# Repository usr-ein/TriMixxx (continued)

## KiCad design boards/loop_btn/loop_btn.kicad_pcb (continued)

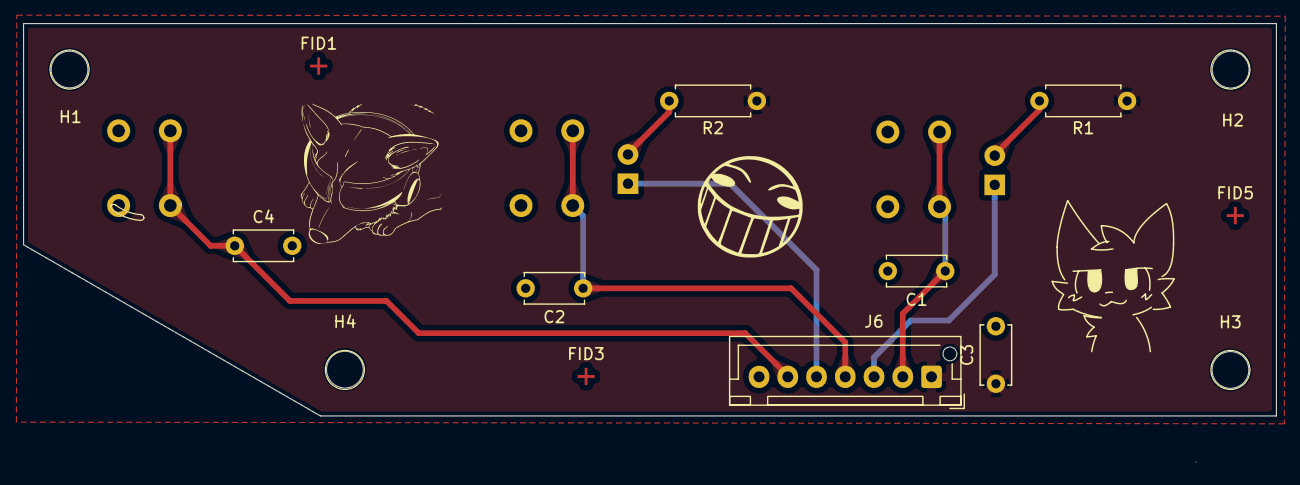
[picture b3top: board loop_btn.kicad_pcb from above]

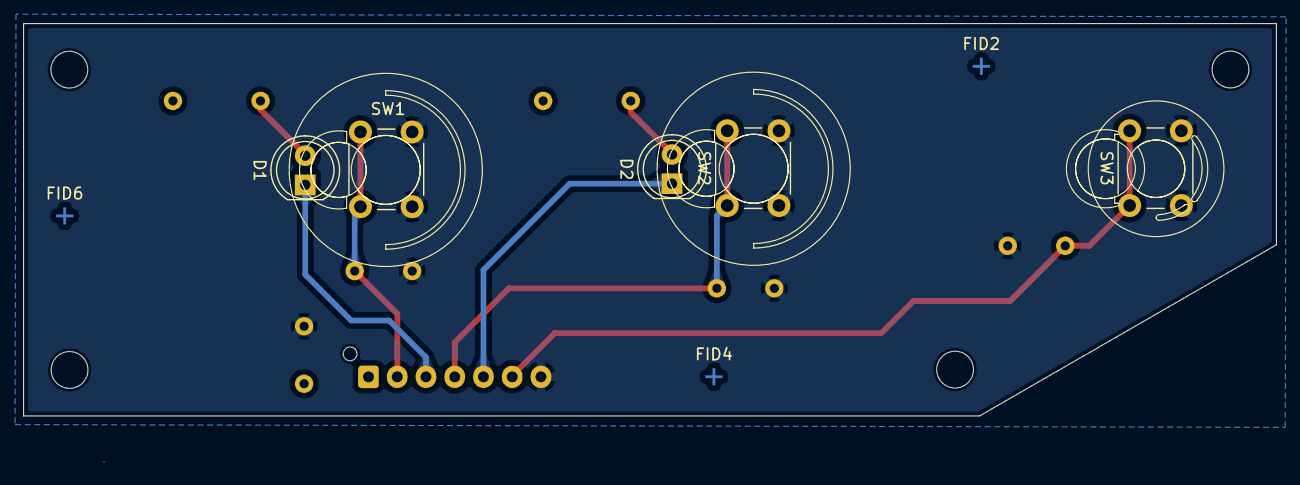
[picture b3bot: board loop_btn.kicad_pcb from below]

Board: 2 copper layers, 109.0 x 34.1 mm, 22 parts (8 on the bottom side), 9 nets.

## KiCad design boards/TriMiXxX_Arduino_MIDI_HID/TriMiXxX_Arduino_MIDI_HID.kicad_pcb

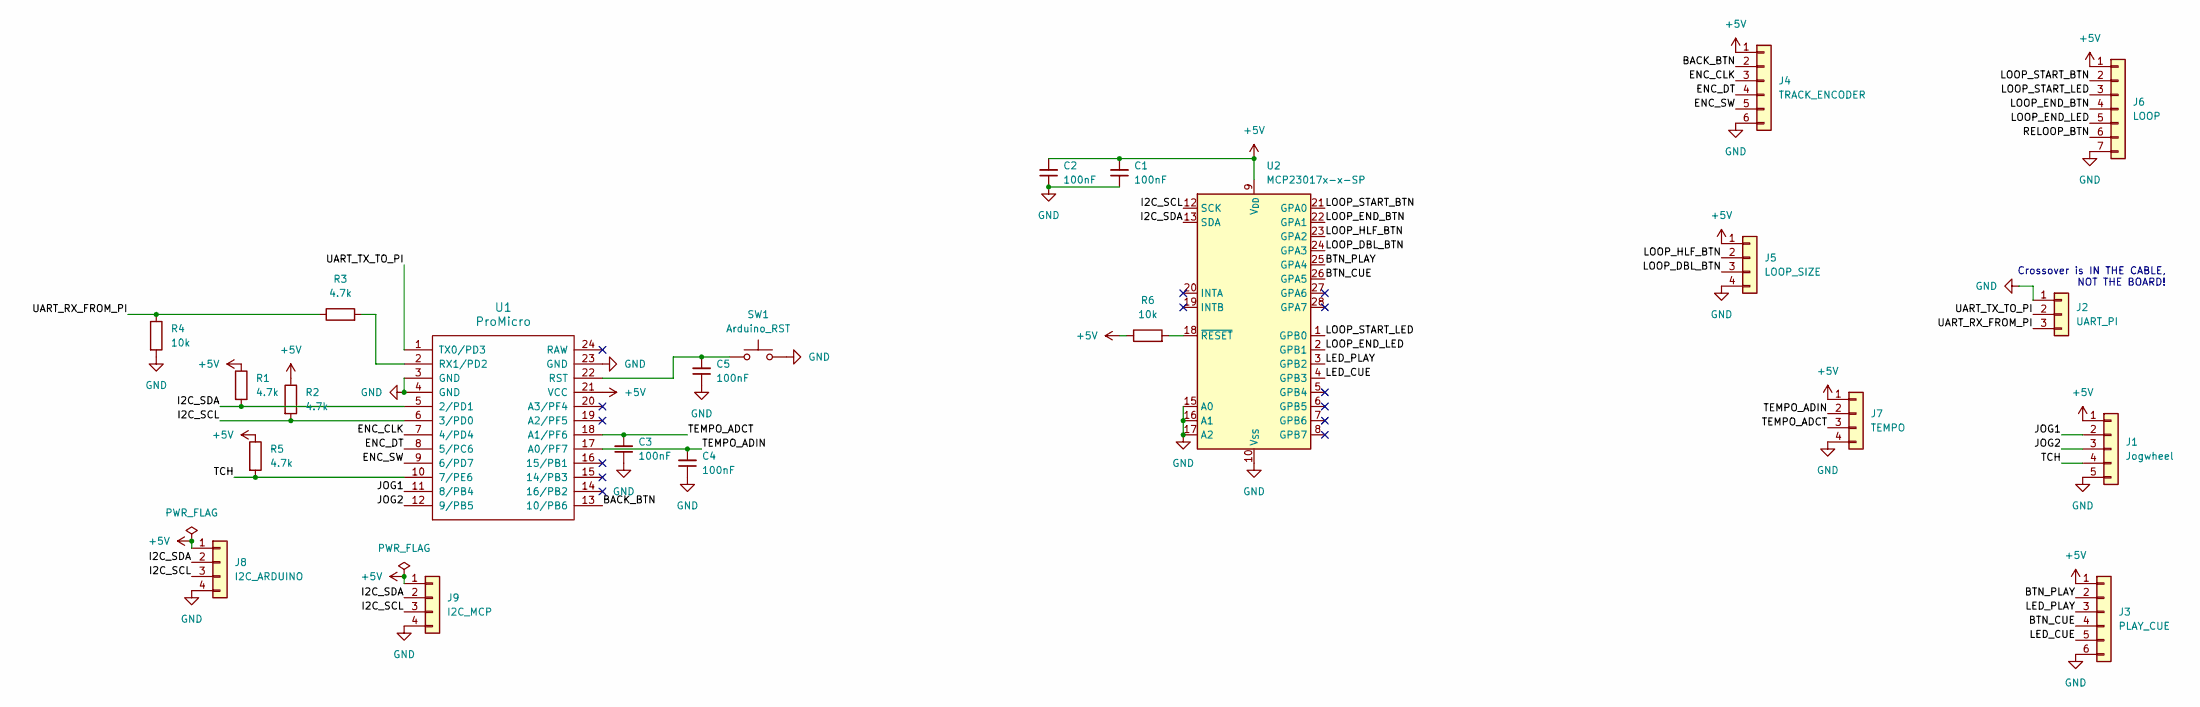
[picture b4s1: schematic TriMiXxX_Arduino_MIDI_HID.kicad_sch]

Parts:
C1, C2, C3, C4, C5: 100nF; C_Disc_D5.0mm_W2.5mm_P5.00mm
J1: Jogwheel; JST_XH_B5B-XH-AM_1x05_P2.50mm_Vertical
J2: UART_PI; JST_XH_B3B-XH-AM_1x03_P2.50mm_Vertical
J3: PLAY_CUE; JST_XH_B6B-XH-AM_1x06_P2.50mm_Vertical
J4: TRACK_ENCODER; JST_XH_B6B-XH-AM_1x06_P2.50mm_Vertical
J5: LOOP_SIZE; JST_XH_B4B-XH-AM_1x04_P2.50mm_Vertical
J6: LOOP; JST_XH_B7B-XH-AM_1x07_P2.50mm_Vertical
J7: TEMPO; JST_XH_B4B-XH-AM_1x04_P2.50mm_Vertical
J8: I2C_ARDUINO; JST_XH_B4B-XH-AM_1x04_P2.50mm_Vertical
J9: I2C_MCP; JST_XH_B4B-XH-AM_1x04_P2.50mm_Vertical
R1, R2, R3, R5: 4.7k; R_Axial_DIN0207_L6.3mm_D2.5mm_P10.16mm_Horizontal
R4, R6: 10k; R_Axial_DIN0207_L6.3mm_D2.5mm_P10.16mm_Horizontal
SW1: Arduino_RST; SW_Push_2P2T_Toggle_CK_PVA2OAH5xxxxxxV2
U1: ProMicro; ArduinoProMicro
U2: MCP23017x-x-SP; DIP-28_W7.62mm

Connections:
+5V: C1.2, C2.2, J1.1, J3.1, J4.1, J5.1, J6.1, J7.1, J8.1, J9.1, R1.1, R2.1, R5.1, R6.1, U1.21 (VCC), U2.9 (V_{DD})
/BACK_BTN: J4.2, U1.13 (10/PB6)
/BTN_CUE: J3.4, U2.26 (GPA5)
/BTN_PLAY: J3.2, U2.25 (GPA4)
/ENC_CLK: J4.3, U1.7 (4/PD4)
/ENC_DT: J4.4, U1.8 (5/PC6)
/ENC_SW: J4.5, U1.9 (6/PD7)
/I2C_SCL: J8.3, J9.3, R2.2, U1.6 (3/PD0), U2.12 (SCK)
/I2C_SDA: J8.2, J9.2, R1.2, U1.5 (2/PD1), U2.13 (SDA)
/JOG1: J1.2, U1.11 (8/PB4)
/JOG2: J1.3, U1.12 (9/PB5)
/LED_CUE: J3.5, U2.4 (GPB3)
/LED_PLAY: J3.3, U2.3 (GPB2)
/LOOP_DBL_BTN: J5.3, U2.24 (GPA3)
/LOOP_END_BTN: J6.4, U2.22 (GPA1)
/LOOP_END_LED: J6.5, U2.2 (GPB1)
/LOOP_HLF_BTN: J5.2, U2.23 (GPA2)
/LOOP_START_BTN: J6.2, U2.21 (GPA0)
/LOOP_START_LED: J6.3, U2.1 (GPB0)
/RELOOP_BTN: J6.6
/TCH: J1.4, R5.2, U1.10 (7/PE6)
/TEMPO_ADCT: C3.2, J7.3, U1.18 (A1/PF6)
/TEMPO_ADIN: C4.2, J7.2, U1.17 (A0/PF7)
/UART_RX_FROM_PI: J2.3, R3.1, R4.1
/UART_TX_TO_PI: J2.2, U1.1 (TX0/PD3)
GND: C1.1, C2.1, C3.1, C4.1, C5.1, J1.5, J2.1, J3.6, J4.6, J5.4, J6.7, J7.4, J8.4, J9.4, R4.2, SW1.2, U1.3 (GND), U1.4 (GND), U1.23 (GND), U2.10 (V_{SS}), U2.15 (A0), U2.16 (A1), U2.17 (A2)
unnamed: C5.2, SW1.1, U1.22 (RST)
unnamed: R3.2, U1.2 (RX1/PD2)
unnamed: R6.2, U2.18 (~RESET)

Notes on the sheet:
Crossover is IN THE CABLE, NOT THE BOARD!

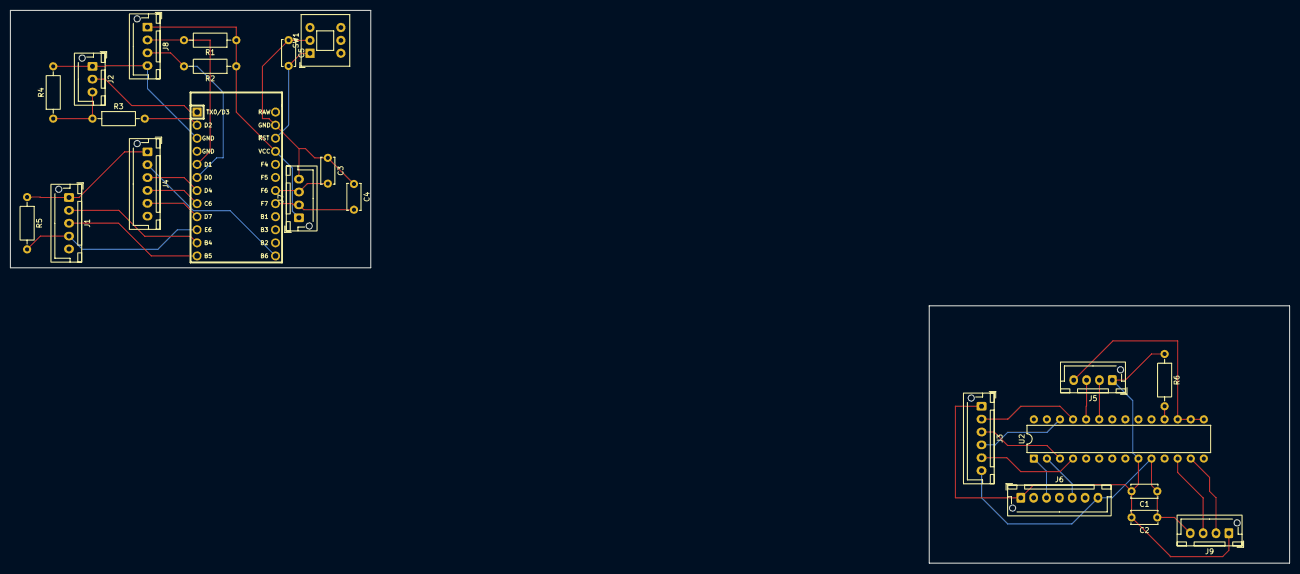
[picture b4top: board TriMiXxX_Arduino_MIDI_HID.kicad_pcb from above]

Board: 4 copper layers, 248.5 x 107.4 mm, 23 parts (0 on the bottom side), 28 nets.

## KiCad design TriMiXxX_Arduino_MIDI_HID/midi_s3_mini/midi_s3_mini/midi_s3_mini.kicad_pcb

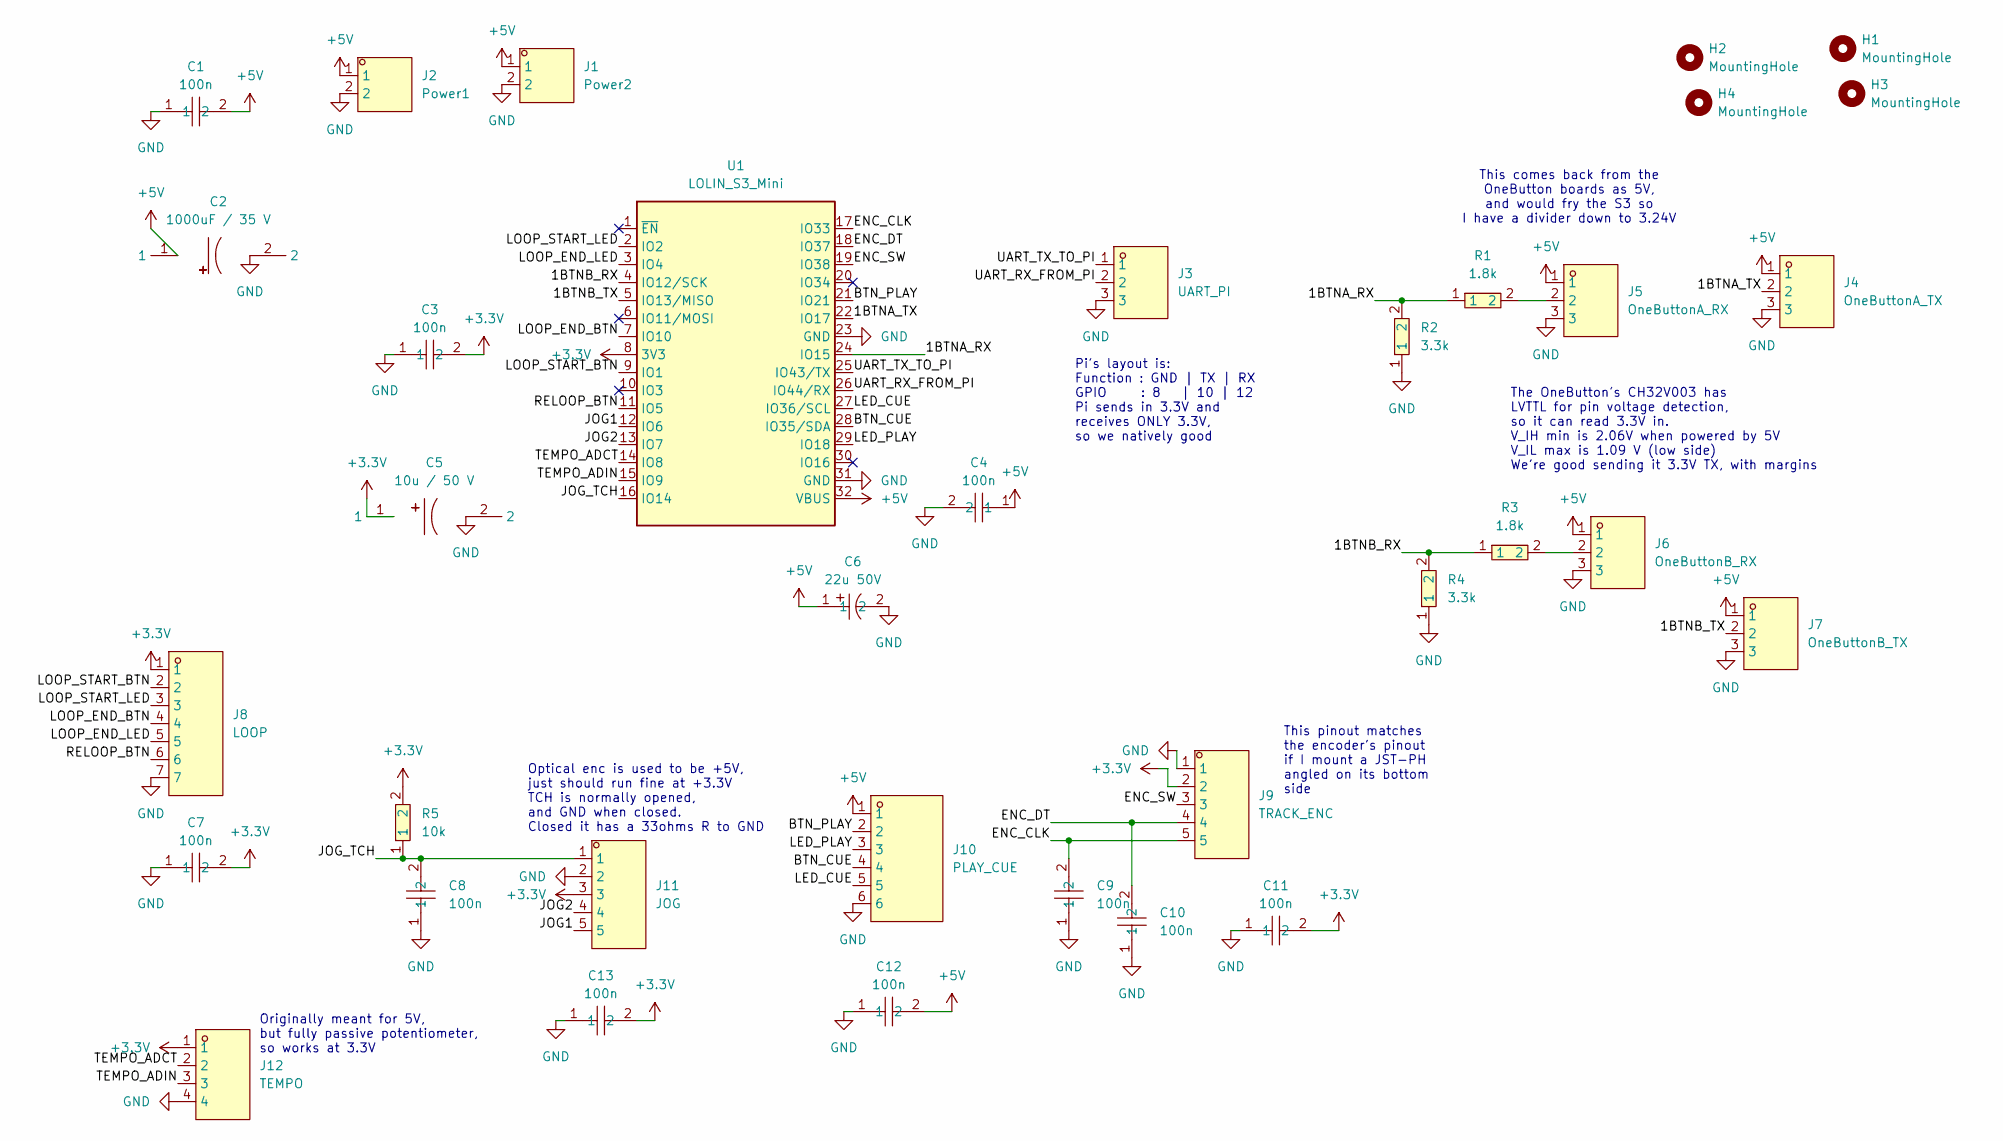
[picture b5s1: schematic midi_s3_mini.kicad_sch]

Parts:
C1, C3, C4, C7, C8, C9, C10, C11, C12, C13: 100n; CAP-TH_L4.2-W3.5-P2.54-D0.5; MPN 178MU0006; LCSC Part C5632430
C2: 1000uF / 35 V; CAP-TH_BD10.0-P5.00-D1.0-FD; MPN ERR1VM102G20OT; LCSC Part C398835
C5: 10u / 50 V; CAP-TH_BD5.0-P2.00-D0.8-FD; MPN 01EC1809SHC10UF50V; LCSC Part C503219
C6: 22u 50V; CAP-TH_BD5.0-P2.00-D0.5-FD; MPN ERG50V22M5X11; LCSC Part C47344185
H1, H2, H3, H4: MountingHole; MountingHole_4.3mm_M4_ISO7380
J1: Power2; CONN-TH_S2B-PH-K-S-LF-SN; MPN S2B-PH-K-S(LF)(SN); LCSC Part C173752
J2: Power1; CONN-TH_S2B-PH-K-S-LF-SN; MPN S2B-PH-K-S(LF)(SN); LCSC Part C173752
J3: UART_PI; CONN-TH_3P-P2.00_S3B-PH-K-S-LF-SN; MPN S3B-PH-K-S(LF)(SN); LCSC Part C157929
J4: OneButtonA_TX; CONN-TH_3P-P2.00_S3B-PH-K-S-LF-SN; MPN S3B-PH-K-S(LF)(SN); LCSC Part C157929
J5: OneButtonA_RX; CONN-TH_3P-P2.00_S3B-PH-K-S-LF-SN; MPN S3B-PH-K-S(LF)(SN); LCSC Part C157929
J6: OneButtonB_RX; CONN-TH_3P-P2.00_S3B-PH-K-S-LF-SN; MPN S3B-PH-K-S(LF)(SN); LCSC Part C157929
J7: OneButtonB_TX; CONN-TH_3P-P2.00_S3B-PH-K-S-LF-SN; MPN S3B-PH-K-S(LF)(SN); LCSC Part C157929
J8: LOOP; CONN-TH_7P-P2.00_S7B-PH-K-S-LF-SN; MPN S7B-PH-K-S(LF)(SN); LCSC Part C157917
J9: TRACK_ENC; CONN-TH_S5B-PH-K-S-LF-SN; MPN S5B-PH-K-S(LF)(SN); LCSC Part C157923
J10: PLAY_CUE; CONN-TH_6P-P2.00_S6B-PH-K-S-LF-SN; MPN S6B-PH-K-S(LF)(SN); LCSC Part C157920
J11: JOG; CONN-TH_S5B-PH-K-S-LF-SN; MPN S5B-PH-K-S(LF)(SN); LCSC Part C157923
J12: TEMPO; CONN-TH_4P-P2.00_S4B-PH-K-S-LF-SN; MPN S4B-PH-K-S(LF)(SN); LCSC Part C157926
R1, R3: 1.8k; RES-TH_BD2.4-L6.3-P10.30-D0.6; MPN MFR-25FTE52-1K8; LCSC Part C172980
R2, R4: 3.3k; RES-TH_BD2.2-L6.5-P10.50-D0.6; MPN MFR0W4F3301A50; LCSC Part C58610
R5: 10k; RES-TH_BD2.5-L6.5-P10.50-D0.6; MPN MFR0W4F1002A50; LCSC Part C57436
U1: LOLIN_S3_Mini

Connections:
+3.3V: C3.2, C5.1, C7.2, C11.2, C13.2, J8.1, J9.2, J11.3, J12.1, R5.2, U1.8 (3V3)
+5V: C1.2, C2.1, C4.1, C6.1, C12.2, J1.1, J2.1, J4.1, J5.1, J6.1, J7.1, J10.1, U1.32 (VBUS)
/1BTNA_RX: R1.1, R2.2, U1.24 (IO15)
/1BTNA_TX: J4.2, U1.22 (IO17)
/1BTNB_RX: R3.1, R4.2, U1.4 (IO12/SCK)
/1BTNB_TX: J7.2, U1.5 (IO13/MISO)
/BTN_CUE: J10.4, U1.28 (IO35/SDA)
/BTN_PLAY: J10.2, U1.21 (IO21)
/ENC_CLK: C9.2, J9.5, U1.17 (IO33)
/ENC_DT: C10.2, J9.4, U1.18 (IO37)
/ENC_SW: J9.3, U1.19 (IO38)
/JOG1: J11.5, U1.12 (IO6)
/JOG2: J11.4, U1.13 (IO7)
/JOG_TCH: C8.2, J11.1, R5.1, U1.16 (IO14)
/LED_CUE: J10.5, U1.27 (IO36/SCL)
/LED_PLAY: J10.3, U1.29 (IO18)
/LOOP_END_BTN: J8.4, U1.7 (IO10)
/LOOP_END_LED: J8.5, U1.3 (IO4)
/LOOP_START_BTN: J8.2, U1.9 (IO1)
/LOOP_START_LED: J8.3, U1.2 (IO2)
/RELOOP_BTN: J8.6, U1.11 (IO5)
/TEMPO_ADCT: J12.2, U1.14 (IO8)
/TEMPO_ADIN: J12.3, U1.15 (IO9)
/UART_RX_FROM_PI: J3.2, U1.26 (IO44/RX)
/UART_TX_TO_PI: J3.1, U1.25 (IO43/TX)
GND: C1.1, C2.2, C3.1, C4.2, C5.2, C6.2, C7.1, C8.1, C9.1, C10.1, C11.1, C12.1, C13.1, J1.2, J2.2, J3.3, J4.3, J5.3, J6.3, J7.3, J8.7, J9.1, J10.6, J11.2, J12.4, R2.1, R4.1, U1.23 (GND), U1.31 (GND)
unnamed: J5.2, R1.2
unnamed: J6.2, R3.2

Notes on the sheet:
Optical enc is used to be +5V, just should run fine at +3.3V TCH is normally opened, and GND when closed. Closed it has a 33ohms R to GND
The OneButton's CH32V003 has LVTTL for pin voltage detection, so it can read 3.3V in. V_IH min is 2.06V when powered by 5V V_IL max is 1.09 V (low side) We're good sending it 3.3V TX, with margins
This comes back from the OneButton boards as 5V, and would fry the S3 so I have a divider down to 3.24V
This pinout matches the encoder's pinout if I mount a JST-PH angled on its bottom side
Pi's layout is: Function : GND | TX | RX GPIO : 8 | 10 | 12 Pi sends in 3.3V and receives ONLY 3.3V, so we natively good
Originally meant for 5V, but fully passive potentiometer, so works at 3.3V

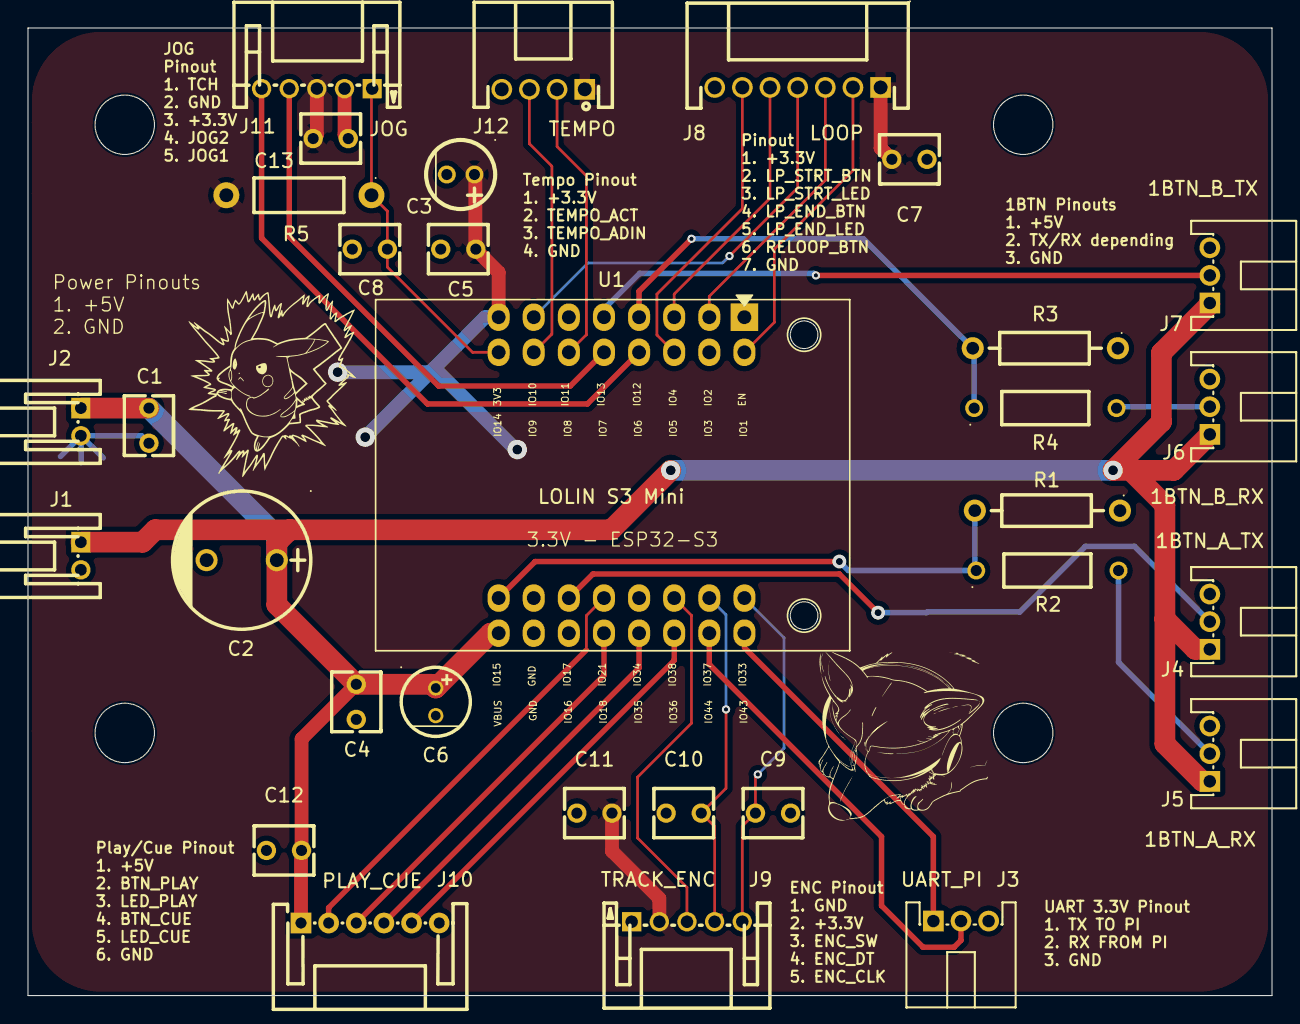
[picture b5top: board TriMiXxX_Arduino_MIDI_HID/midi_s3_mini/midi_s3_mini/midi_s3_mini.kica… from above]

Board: 2 copper layers, 90.0 x 70.0 mm, 35 parts (0 on the bottom side), 28 nets.

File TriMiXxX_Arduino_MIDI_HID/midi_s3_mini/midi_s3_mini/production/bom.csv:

Designator,Footprint,Quantity,Value,LCSC Part #
"C1, C10, C11, C12, C13, C3, C4, C7, C8, C9",CAP-TH_L4.2-W3.5-P2.54-D0.5,10,100n,C5632430
C2,CAP-TH_BD10.0-P5.00-D1.0-FD,1,1000uF / 35 V,C398835
C5,CAP-TH_BD5.0-P2.00-D0.8-FD,1,10u / 50 V,C503219
C6,CAP-TH_BD5.0-P2.00-D0.5-FD,1,22u 50V,C47344185
J1,CONN-TH_S2B-PH-K-S-LF-SN,1,Power2,C173752
J10,CONN-TH_6P-P2.00_S6B-PH-K-S-LF-SN,1,PLAY_CUE,C157920
J11,CONN-TH_S5B-PH-K-S-LF-SN,1,JOG,C157923
J12,CONN-TH_4P-P2.00_S4B-PH-K-S-LF-SN,1,TEMPO,C157926
J2,CONN-TH_S2B-PH-K-S-LF-SN,1,Power1,C173752
J3,CONN-TH_3P-P2.00_S3B-PH-K-S-LF-SN,1,UART_PI,C157929
J4,CONN-TH_3P-P2.00_S3B-PH-K-S-LF-SN,1,1BTN_A_TX,C157929
J5,CONN-TH_3P-P2.00_S3B-PH-K-S-LF-SN,1,1BTN_A_RX,C157929
J6,CONN-TH_3P-P2.00_S3B-PH-K-S-LF-SN,1,1BTN_B_RX,C157929
J7,CONN-TH_3P-P2.00_S3B-PH-K-S-LF-SN,1,1BTN_B_TX,C157929
J8,CONN-TH_7P-P2.00_S7B-PH-K-S-LF-SN,1,LOOP,C157917
J9,CONN-TH_S5B-PH-K-S-LF-SN,1,TRACK_ENC,C157923
"R1, R3",RES-TH_BD2.4-L6.3-P10.30-D0.6,2,1.8k,C172980
"R2, R4",RES-TH_BD2.2-L6.5-P10.50-D0.6,2,3.3k,C58610
R5,RES-TH_BD2.5-L6.5-P10.50-D0.6,1,10k,C57436
U1,LOLIN_S3_Mini,1,LOLIN_S3_Mini,

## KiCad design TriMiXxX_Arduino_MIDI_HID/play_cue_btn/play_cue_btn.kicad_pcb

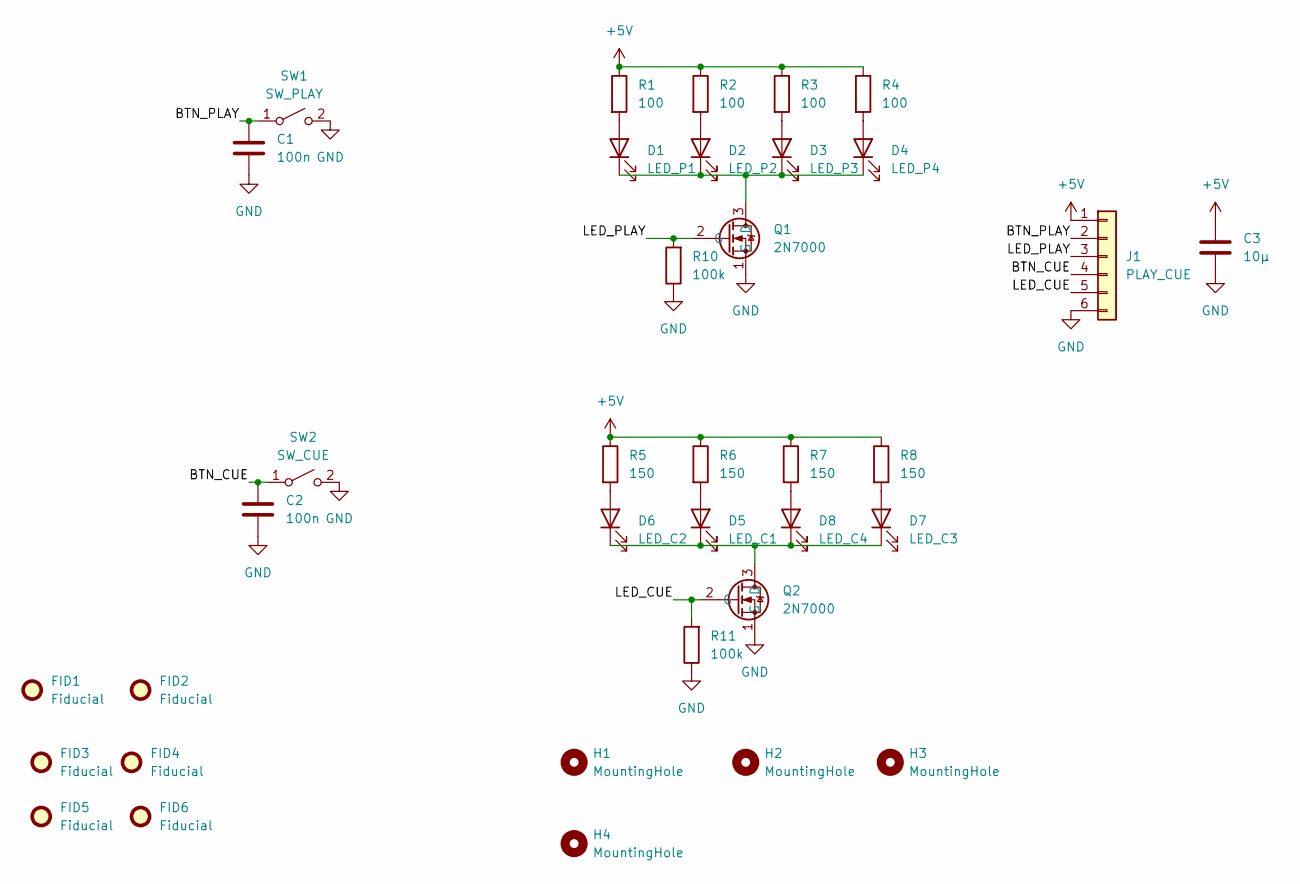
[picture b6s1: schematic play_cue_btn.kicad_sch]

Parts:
C1, C2: 100n; C_Disc_D5.0mm_W2.5mm_P5.00mm
C3: 10µ; C_Disc_D5.0mm_W2.5mm_P5.00mm
D1: LED_P1; LED_D5.0mm
D2: LED_P2; LED_D5.0mm
D3: LED_P3; LED_D5.0mm
D4: LED_P4; LED_D5.0mm
D5: LED_C1; LED_D5.0mm
D6: LED_C2; LED_D5.0mm
D7: LED_C3; LED_D5.0mm
D8: LED_C4; LED_D5.0mm
FID1, FID2, FID3, FID4, FID5, FID6: Fiducial; Fiducial_Cross_1.5mm_Mask2mm
H1, H2, H3, H4: MountingHole; MountingHole_3.2mm_M3
J1: PLAY_CUE; JST_PH_B6B-PH-K_1x06_P2.00mm_Vertical
Q1, Q2: 2N7000; TO-92_Inline
R1, R2, R3, R4: 100; R_Axial_DIN0207_L6.3mm_D2.5mm_P7.62mm_Horizontal
R5, R6, R7, R8: 150; R_Axial_DIN0207_L6.3mm_D2.5mm_P7.62mm_Horizontal
R10, R11: 100k; R_Axial_DIN0207_L6.3mm_D2.5mm_P7.62mm_Horizontal
SW1: SW_PLAY; SW_PUSH_6mm_H4.3mm
SW2: SW_CUE; SW_PUSH_6mm_H4.3mm

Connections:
+5V: C3.1, J1.1, R1.1, R2.1, R3.1, R4.1, R5.1, R6.1, R7.1, R8.1
/BTN_CUE: C2.1, J1.4, SW2.1 (A)
/BTN_PLAY: C1.1, J1.2, SW1.1 (A)
/LED_CUE: J1.5, Q2.2 (G), R11.2
/LED_PLAY: J1.3, Q1.2 (G), R10.2
GND: C1.2, C2.2, C3.2, J1.6, Q1.1 (S), Q2.1 (S), R10.1, R11.1, SW1.2 (B), SW2.2 (B)
unnamed: D1.2 (A), R1.2
unnamed: D1.1 (K), D2.1 (K), D3.1 (K), D4.1 (K), Q1.3 (D)
unnamed: D2.2 (A), R2.2
unnamed: D3.2 (A), R3.2
unnamed: D4.2 (A), R4.2
unnamed: D5.2 (A), R6.2
unnamed: D5.1 (K), D6.1 (K), D7.1 (K), D8.1 (K), Q2.3 (D)
unnamed: D6.2 (A), R5.2
unnamed: D7.2 (A), R8.2
unnamed: D8.2 (A), R7.2

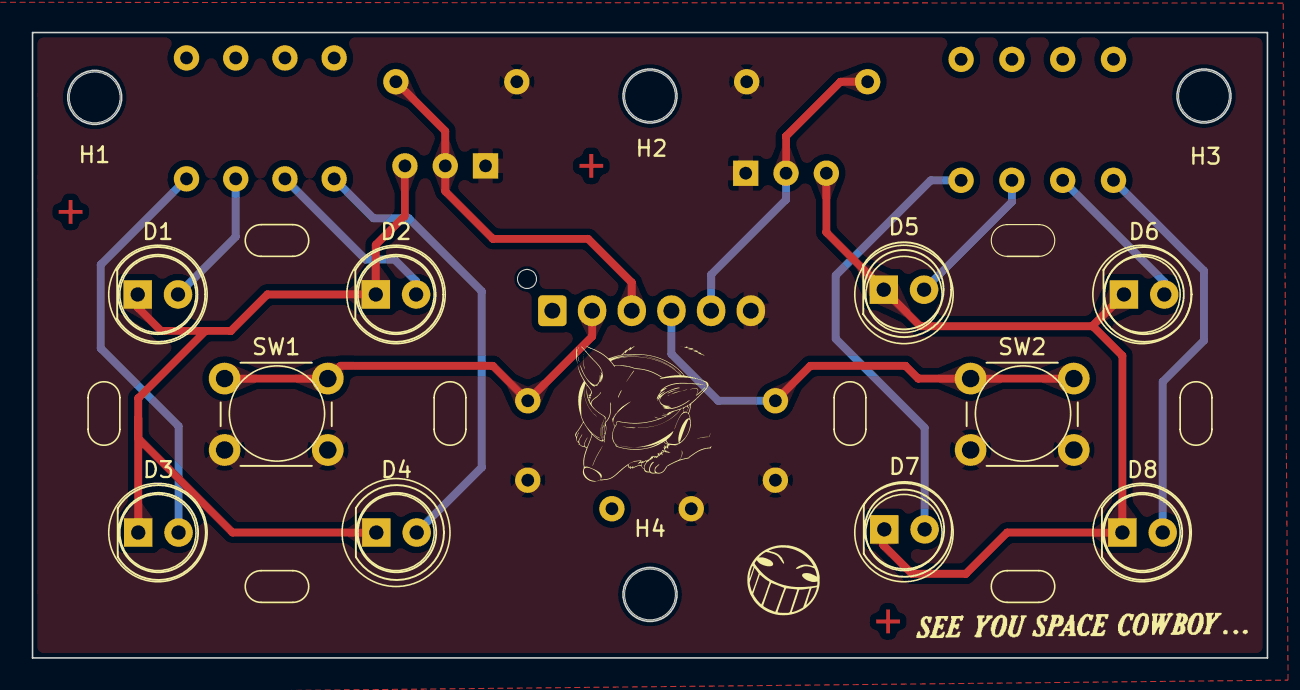
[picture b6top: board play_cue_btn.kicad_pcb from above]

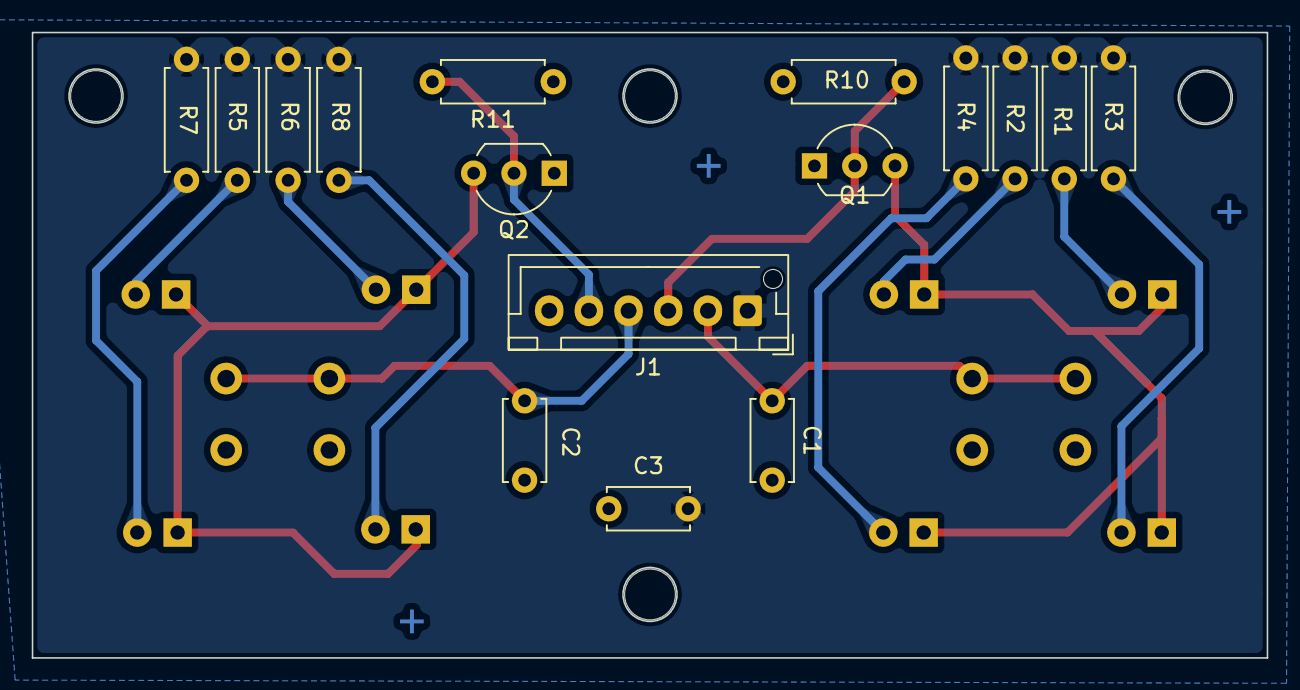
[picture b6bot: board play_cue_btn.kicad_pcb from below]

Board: 2 copper layers, 77.8 x 39.4 mm, 36 parts (19 on the bottom side), 16 nets.
